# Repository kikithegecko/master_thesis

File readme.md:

### Casual Interation with a Bracelet

Yes, this is my Master thesis. It is about interaction with
a wrist-worn wearable (aka bracelet) and encompassed the
whole design and manufacturing process from the bracelet
itself to the needed electronics, some minituarization steps,
and of course the software. Oh, and the writing.

Here are some buzzwords if you're interested but want to know
if looking through all those files is really worth it ;)

- CAD models for 3D printing
- CAD models for liquid silicone cast
- PCB schematics for Teensy and Arduino shields
- Embedded code for a Bluetooth-controlled RGB light source
- A working implementation of the [3$ Gesture Recognizer](http://www.medien.ifi.lmu.de/pubdb/publications/pub/kratz2010threedollar/kratz2010threedollar.pdf) featuring 3-dimensional Golden Section Search
- A huge LaTeX writeup with lots of progress pictures
- Some slide sets to be used with reveal.js

If you're just interested in pictures, take a loog at my
[flickr profile](https://www.flickr.com/photos/kikidergecko/sets/), I have outsourced all pictures there.

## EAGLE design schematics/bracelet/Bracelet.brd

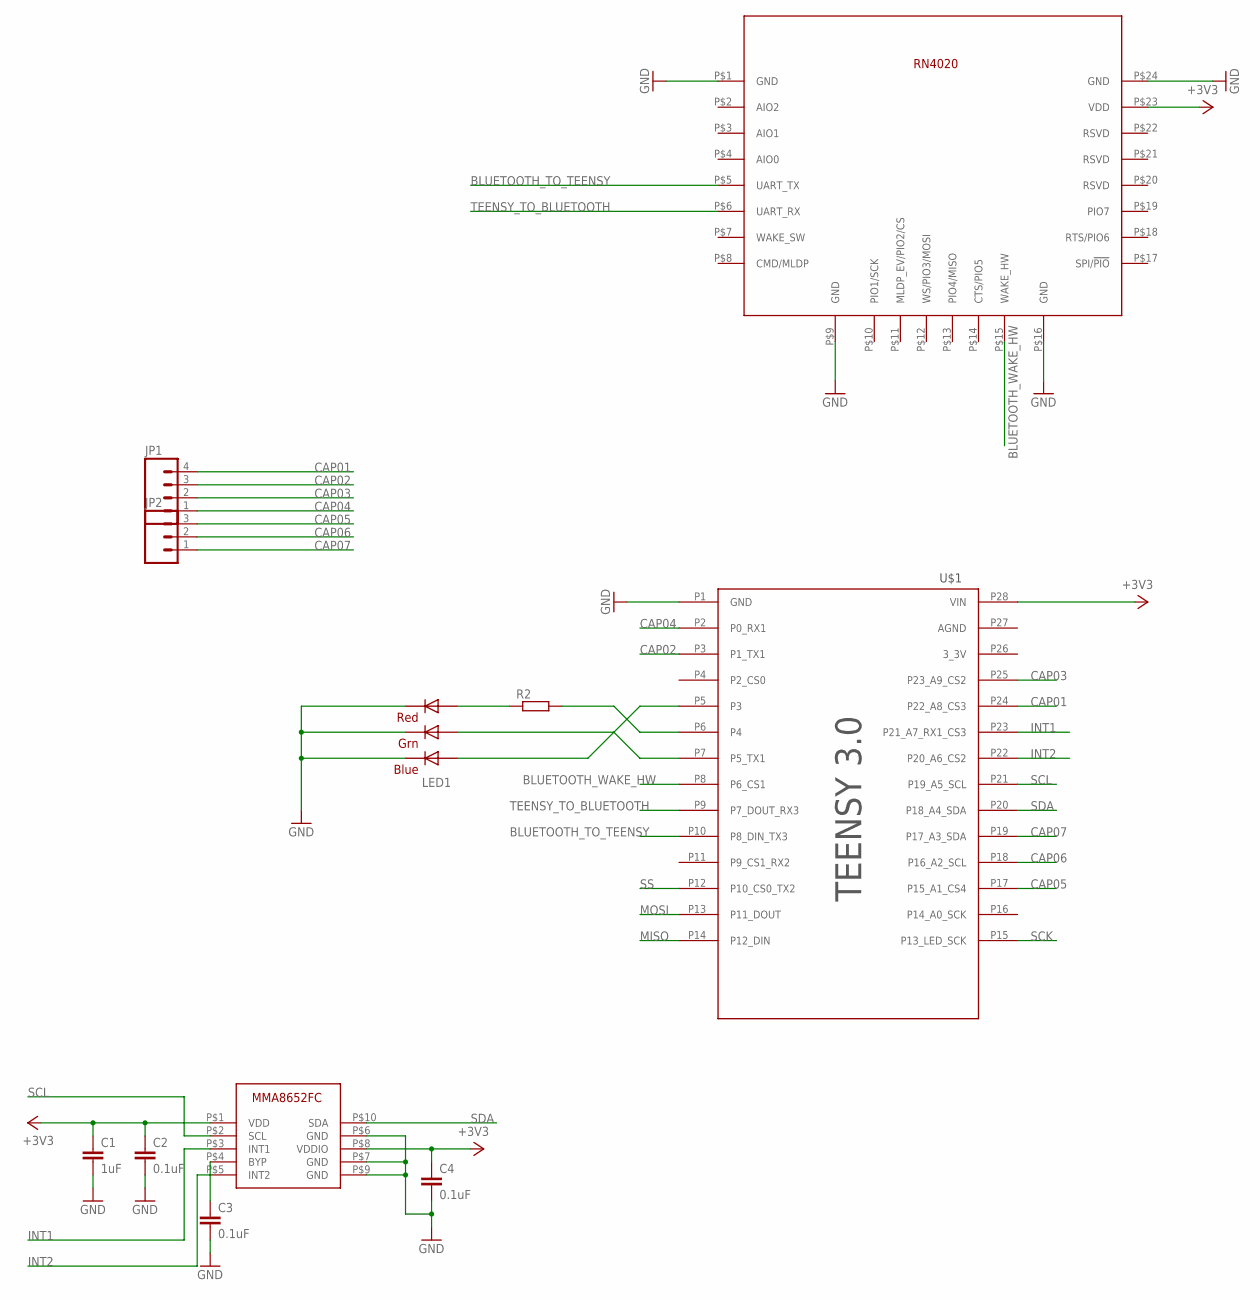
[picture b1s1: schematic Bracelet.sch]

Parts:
C1: 1uF; C0805
C2, C3, C4: 0.1uF; C0805
JP1: M04PTH; 1X04
JP2: M03PTH; 1X03
LED1: RGBLED5050
R2: R-EU_R0805; R0805
RN4020: RN4020
U$1: TEENSY3; TEENSY3_BRD
U$3: MMA8652FC

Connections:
+3V3: C1.1, C2.1, C4.1, RN4020.P$23 (VDD), U$1.P28 (VIN), U$3.P$1 (VDD), U$3.P$8 (VDDIO)
BLUETOOTH_TO_TEENSY: RN4020.P$5 (UART_TX), U$1.P10 (P8_DIN_TX3)
BLUETOOTH_WAKE_HW: RN4020.P$15 (WAKE_HW), U$1.P8 (P6_CS1)
CAP01: JP1.4, U$1.P24 (P22_A8_CS3)
CAP02: JP1.3, U$1.P3 (P1_TX1)
CAP03: JP1.2, U$1.P25 (P23_A9_CS2)
CAP04: JP1.1, U$1.P2 (P0_RX1)
CAP05: JP2.3, U$1.P17 (P15_A1_CS4)
CAP06: JP2.2, U$1.P18 (P16_A2_SCL)
CAP07: JP2.1, U$1.P19 (P17_A3_SDA)
GND: C1.2, C2.2, C3.2, C4.2, LED1.4 (BLUE_C), LED1.5 (RED_C), LED1.6 (GREEN_C), RN4020.P$1 (GND), RN4020.P$9 (GND), RN4020.P$16 (GND), RN4020.P$24 (GND), U$1.P1 (GND), U$3.P$6 (GND), U$3.P$7 (GND), U$3.P$9 (GND)
INT1: U$1.P23 (P21_A7_RX1_CS3), U$3.P$3 (INT1)
INT2: U$1.P22 (P20_A6_CS2), U$3.P$5 (INT2)
MISO: U$1.P14 (P12_DIN)
MOSI: U$1.P13 (P11_DOUT)
unnamed: C3.1, U$3.P$4 (BYP)
unnamed: LED1.2 (RED_A), R2.1
unnamed: R2.2, U$1.P6 (P4)
unnamed: LED1.3 (BLUE_A), U$1.P5 (P3)
unnamed: LED1.1 (GREEN_A), U$1.P7 (P5_TX1)
SCK: U$1.P15 (P13_LED_SCK)
SCL: U$1.P21 (P19_A5_SCL), U$3.P$2 (SCL)
SDA: U$1.P20 (P18_A4_SDA), U$3.P$10 (SDA)
SS: U$1.P12 (P10_CS0_TX2)
TEENSY_TO_BLUETOOTH: RN4020.P$6 (UART_RX), U$1.P9 (P7_DOUT_RX3)

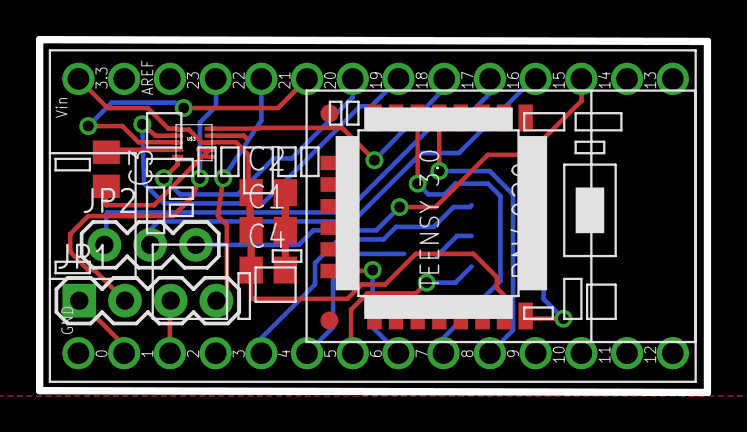
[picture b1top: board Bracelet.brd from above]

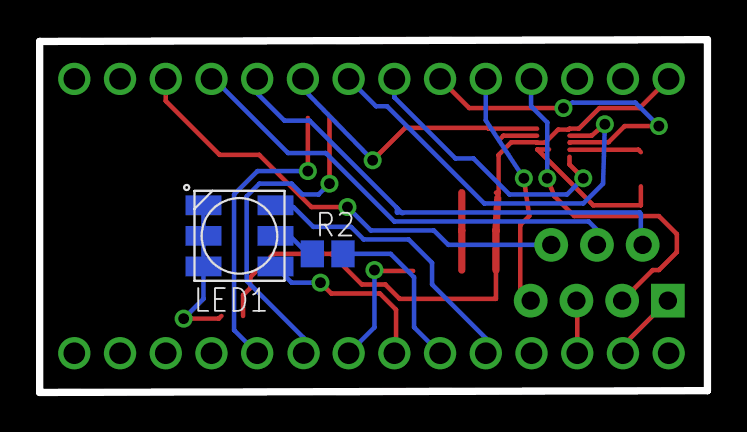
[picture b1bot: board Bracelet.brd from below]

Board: 2 copper layers, 37.1 x 19.6 mm, 11 parts (2 on the bottom side), 21 nets.

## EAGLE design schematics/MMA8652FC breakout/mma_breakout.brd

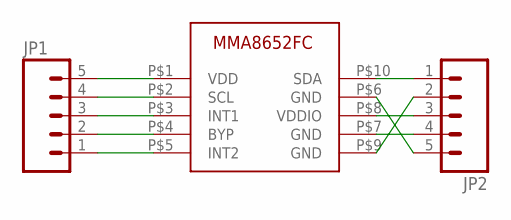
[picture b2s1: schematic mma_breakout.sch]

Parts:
JP1, JP2: M05PTH; 1X05
U$1: MMA8652FC

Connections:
unnamed: JP1.5, U$1.P$1 (VDD)
unnamed: JP1.4, U$1.P$2 (SCL)
unnamed: JP2.5, U$1.P$6 (GND)
unnamed: JP2.4, U$1.P$7 (GND)
unnamed: JP1.1, U$1.P$5 (INT2)
unnamed: JP2.1, U$1.P$10 (SDA)
unnamed: JP1.3, U$1.P$3 (INT1)
unnamed: JP1.2, U$1.P$4 (BYP)
unnamed: JP2.3, U$1.P$8 (VDDIO)
unnamed: JP2.2, U$1.P$9 (GND)

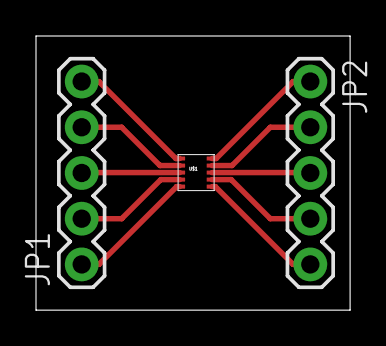
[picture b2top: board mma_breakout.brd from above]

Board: 2 copper layers, 17.4 x 15.2 mm, 3 parts (0 on the bottom side), 10 nets.

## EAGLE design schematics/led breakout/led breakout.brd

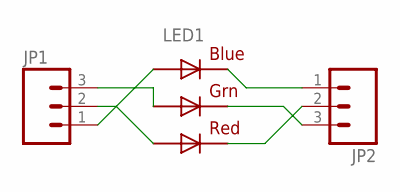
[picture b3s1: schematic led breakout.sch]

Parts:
JP1, JP2: M03PTH; 1X03
LED1: RGBLED5050

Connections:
unnamed: JP1.3, LED1.1 (GREEN_A)
unnamed: JP1.2, LED1.2 (RED_A)
unnamed: JP1.1, LED1.3 (BLUE_A)
unnamed: JP2.1, LED1.4 (BLUE_C)
unnamed: JP2.2, LED1.5 (RED_C)
unnamed: JP2.3, LED1.6 (GREEN_C)

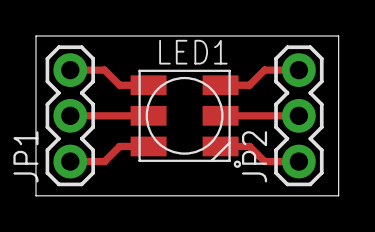
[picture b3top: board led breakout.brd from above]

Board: 2 copper layers, 16.8 x 8.9 mm, 3 parts (0 on the bottom side), 6 nets.

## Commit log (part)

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2014-05-20 added freecad files and stl of first prototype model
2014-05-20 added freecad files and stl of second prototype
    a more comfortable cuff with smaller and flatter ends.
2014-05-20 added solidworks and stl files for amico bracelet
    source:
    https://grabcad.com/library/amico-bracelet--9
    by Daniel Muschke
2014-05-20 added freecad and stl files for a tri-part model
    the stl files have some issues on the mirror axis.
2014-05-20 missed a fusion which resulted in bad stl files
2014-05-23 added gitignore file
2014-05-23 new revision of tri part bracelet
    features:
    - bigger (actually wearable)
    - additional holes for wiring
    turned out to be too big :/
2014-06-16 Cuff with lid, also increased the diameter.
2014-07-02 updated gitignore with LaTeX stuff.
2014-07-02 renaming of main document and some cleanup... probably.
2014-07-02 arduino code for the lamp thingy
2014-07-02 color change via serial.
2014-07-04 Changed lamp communication syntax from "RRR GGG BBB" to "RRRGGGBBB". Who needs spaces anyways?
2014-07-07 Running into bluetooth issues -.-
2014-07-07 Outsourcing some chapters. Started with text from the wiki page.
2014-07-09 strangely those aren't ignored...
2014-07-09 Bluetooth light control works! :D
2014-07-09 Schematic for the Lamp setup.
2014-07-09 fading! :D
2014-07-10 silicone bracelet and mold
2014-07-10 new mold, round.
2014-07-16 new mold
2014-07-21 new silicone mold.
2014-07-21 adaption to the manufactured pcb. doesn't work yet.
2014-07-23 switching back to software serial for bluetooth.
2014-07-23 switching back to softwareserial.
2014-07-31 arduino lamp stuff
2014-07-31 slides for reveal.js and content
2014-08-01 Continued writing.
2014-08-06 error corrections and more writing.
2014-08-06 new blank chapter for related work.
2014-08-14 touch slider code for teensy by henning
2014-08-14 svg schematic for a touch slider
2014-08-14 3d accelerometer testing code.
2014-08-18 setting analog input pins to "input" makes your software behave strangely. also some configuration and cleanup.
2014-08-18 recorded some test data and made a plot. looks... interesting.
2014-08-20 preperations for gesture recognition: sample on button press. next step: save data somewhere, build a knowledge base, implement gesture recognition algorithm.
2014-08-21 more sample records
2014-08-21 some experimentations and gesture recording.
    next: how to store some kind of knowledge base on the teensy.
2014-08-27 Wrote part about CAD.
2014-08-27 Fixed typo.
2014-08-27 printing section
2014-08-27 started silicone section
2014-09-01 working state
2014-09-01 first table (shore hardness)
2014-09-01 finished silicone section and added a picture
2014-09-04 bibliography imported from docear. Added some web resources
2014-09-04 now with (some) citations! Maybe I should change the style.
2014-09-05 bounding box for 1$, should be finished for 2d. now feed some data.
2014-09-19 some writing
2014-09-19 hope this works
2014-09-20 new bib entry
2014-09-22 refactored resample function
2014-09-22 fixed some loops
2014-09-22 more refactoring
2014-09-24 RGB LED breakout board files and stuff. Successfully etched!
2014-09-26 ignores for eagle files
2014-09-26 and some more
2014-09-26 Had wrong pin headers (too small), but worked out since the difference is not that big and there are only 3 pins on each side.
2014-09-26 New breakout board for MMA8652 digital accelerometer.
2014-09-26 added RGB LED test lines.
2014-09-26 added some pictures
2014-09-26 added some sections
2014-09-27 finished segmented bracelet section
2014-09-27 some cleanup. Those files were used in the classicthesis template and are not needed any more.
2014-09-27 forgot one.
2014-09-30 stencil files for mma breakout board
2014-10-01 yet another stencil file I used for successful laser cutting
2014-10-02 minimal test script for the digital accelerometer breakout board. receives only zeroes atm.
2014-10-06 tried some things, still no success.
2014-10-07 started with some helper functions for accelerometer config and control.
2014-10-07 did some testing, nothing woks. even active mode does not set. checked the wiring and everything seems to be ok.
2014-10-09 reworked lamp chapter
2014-10-09 added picture of lamp. could be improved...
2014-10-09 changed library to the modified version of Wire for Teensy.
    Read works!
2014-10-09 bugfix: two function names were switched -.-
    also changed types from byte to uint8_t because
    that's what comes out of the (new) Wire functions.
    Some cleanup and testing, works fine.
2014-10-09 a little more cleanup, nothing important.
2014-10-09 code for reading acceleration data and converting to signed int numbers.
    refuses to compile with "stuct does not name a type" error. sigh.
2014-10-10 fix struct error and removed some debug lines.
2014-10-10 finished layout, accel pullups need to be conf'ed to internal.
2014-10-10 activated internal pullup resistors
2014-10-10 added a simple pushbutton for increased number of options. I strongly hope that we own smd 2-pin pushbuttons in stock...
2014-10-13 finished bracelet design and etched a board.
2014-10-15 new bracelet version with slightly broader wires next to the accelerometer. since they always broke :(
2014-10-15 updated laser svgs accordingly.
2014-10-15 generated stencil files and removed switch and bluetooth pads.
2014-10-16 new bracelet version! - new teensy only with needed pads - no button - no unnecessary multipliers at the LED - broader circuits - pcb is much smaller
2014-10-17 added z tap detection.
    works, but is very sensitive atm. next idea: use high-pass filtered data.
2014-10-17 configured tap sensing to be less sensitive.
2014-10-17 added some tap configs.
    still not working as intended, especially double tap detection fails.
2014-10-17 new pictures, reduced size significantly
2014-10-20 some parameter fiddling for accelerometer calibration
2014-10-20 new cad model for teensy with shield.
2014-10-22 new cad model for a new cast.
2014-10-22 some tap sensitivity config
2014-10-23 comments and gesture recognition preparations
2014-10-27 some debug output to serial
2014-10-27 stuff
2014-10-28 work in progress, gesture stuff.
2014-10-30 cleanup iteration.
2014-10-30 onedollar to threedollar. not complete yet.
2014-10-31 porting the one dollar algorithm to the three dollar algorithm.
    GSS is the last big issue, afterwards testing can begin.
2014-10-31 added sample data for some gestures
    those were recorded wearing the current bracelet
    prototype. sould be okay for testing the 3$ recognizer
2014-11-03 debug output for gesture recording
2014-11-03 fixed a little error
2014-11-03 renamed circle gesture file for consistency reasons
2014-11-03 started implementing the actual recognizer and encountered some errors.
    will fix them tomorrow.
2014-11-03 some ideas for writing down the gesture recognition algorithm section
2014-11-04 bugfixing
2014-11-04 code runs, but returns strange results.
2014-11-04 some further investigation shows that the recorded data looks like crap.
2014-11-05 plotting foo
2014-11-05 helper script for recording gesture data of random ppl
2014-11-06 tiny bits of words
2014-11-06 next revision for braclet board, now dual layer.
2014-11-06 finished board layout and created gerber files.
2014-11-06 some more tiny words
2014-11-07 new stencil files
2014-11-07 skeleton file for teensy project extension
2014-11-08 excluded some eagle dotfiles from gitignore
    not sure which are necessary for pcb manufacturing....
2014-11-08 more writing
2014-11-10 new bib entry, removed corresponding todo.
2014-11-10 disabled high-pass filtering and recorded some test data
    1-10 are a 90° angle, 11-20 are arcs and 21-30 are circles.
    plotted and looks quite okay, but here and there
    are some outliers.
    possibly the accelerometer wasn't soldered properly.
2014-11-10 somehow this wasn't comitted before.
2014-11-11 reorganized test data for gesture thingy.
2014-11-11 work in progress.
    recognizing is wrong atm, probably due to bad rotation.
    I picked up a matrix from the 3$ reference implementation
    and can derive Euler axis and angle from that.
    Tomorrow will be algebra-day!
2014-11-12 It works!!! :D
2014-11-12 started arduino/c port.
2014-11-12 commented out some debug prints.
2014-11-13 enabled HPF again and corrected some recognizer code for teensy
2014-11-13 new ref and some writing
2014-11-13 minor stuff.
2014-11-14 added some bluetooth code
2014-11-14 recorded sample gesturs: Z, O and loop
2014-11-15 modified data recording script for use with linux
2014-11-18 new bracelet
2014-11-18 touch slider svg
2014-11-19 reworked scenario chapter
2014-11-19 little programming
2014-11-21 added touch slider code.
2014-11-24 writing.
2014-11-24 code
2014-11-25 minor writing
2014-12-01 Some comments
2014-12-01 coding. pronation detection is cumbersome.
2014-12-02 started reworking according to Henning's annotations.
2014-12-02 continuted corrections
2014-12-02 rotation detection almost done. needs to take more history in account and think of a threshold value to consider it pronation.
2014-12-03 pronation/supination works.
2014-12-03 finished reworking according to annotations
2014-12-03 commented out a renewcommand line with comment "fix list of acronyms". apparently this fix isn't needed any more.
2014-12-04 various changes:
    * slider -> tslider
    * rotation: changed min to mean for on/off detect
    * introduced constant for magic number (could still be improved)
    * color mood change (actual color change still stubby)
    * hue change code, actual hsv->rgb still stubby.
    This means: all interaction techniques are implemented! \o/
2014-12-05 cleanup and comments.
2014-12-08 some dirty fix for incorrect lengths and a division by zero fi.
2014-12-08 some code to pick the best templates from the recorded gestures
    not sure if this works as intended with more than one template per
    gesture.
2014-12-08 new python script for bluetooth comm between bracelet and lamp
2014-12-08 improved and refined the template picking code.
2014-12-09 reworked prototype sections and wrote touch sensor section and started accelerometer section.
2014-12-09 prepare for second pass
2014-12-09 wrote hsl->rgb, changed hsv to hsl where it occured
2014-12-09 added blacklist for template picking, so that gestures that already are templates won't get recommended again.
2014-12-09 fixed hsv stuff by pasting some code. added lamp output. still some todos left.
2014-12-09 added some todos in interaction chapter.
2014-12-09 some rgb filtering code
2014-12-10 minimal test for bluetooth gateway, copy of the onedollar lib and some corrections. should work.
2014-12-10 wrote related work section.
2014-12-11 added dimming and on/off code. untested.
2014-12-11 very little writing
2014-12-11 writing, some new pictures, an improved picture and a new reference for i2c.
2014-12-13 work of the day
2014-12-14 today's work.
2014-12-15 added hsl2rgb algorithm, some minor stuff in intaction text
2014-12-15 new pictures for color spaces
2014-12-15 Some comments on interaction intro
2014-12-15 another template picking metric: correct/fp ratio
2014-12-15 corrections and writing
2014-12-16 lots of writing, some chapter merging, some headline renames
2014-12-16 removed some todos, improved math formatting
2014-12-16 Code is now finished. Gesture detection is not as reliable, but I will end working on this until deadline.
2014-12-16 renames and new pictures.
2014-12-17 finished writing \o/
2014-12-17 a ton of pictures!
2014-12-18 rework bib part 1
2014-12-18 checked bib entries, to cleaning yet
2014-12-18 wrote abstract in English and German. Final.
2014-12-18 title page and intro ready.
2014-12-18 extension of related work. renamed a paper.
2014-12-18 current state bulk commit
2014-12-18 another bulk commit
2014-12-19 sorted acronyms
2014-12-19 abstract FINAL!
2014-12-19 introduction FINAL!
2014-12-19 related work FINAL!
2014-12-19 bracelet chapter FINAL!
2014-12-19 light source chapter FINAL!
2014-12-19 interaction chapter FINAL!
2014-12-19 icons for gestures
2014-12-19 evaluation chapter FINAL!
2014-12-19 found one error in picture description
2014-12-19 writing FINAL!
2015-01-22 final presentation, first draft
2015-02-06 slides nearly finished, content set.
2015-05-14 outsourced breakout boards
2015-05-14 removed unused graphics from latex folder
2015-05-14 deleted tracked aux files
2015-05-14 added texstudio session and pyc to gitignore

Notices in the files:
parts and their libraries:
SparkFun-Connectors: Licensing: Creative Commons ShareAlike 4.0 International - https://creativecommons.org/licenses/by-sa/4.0
